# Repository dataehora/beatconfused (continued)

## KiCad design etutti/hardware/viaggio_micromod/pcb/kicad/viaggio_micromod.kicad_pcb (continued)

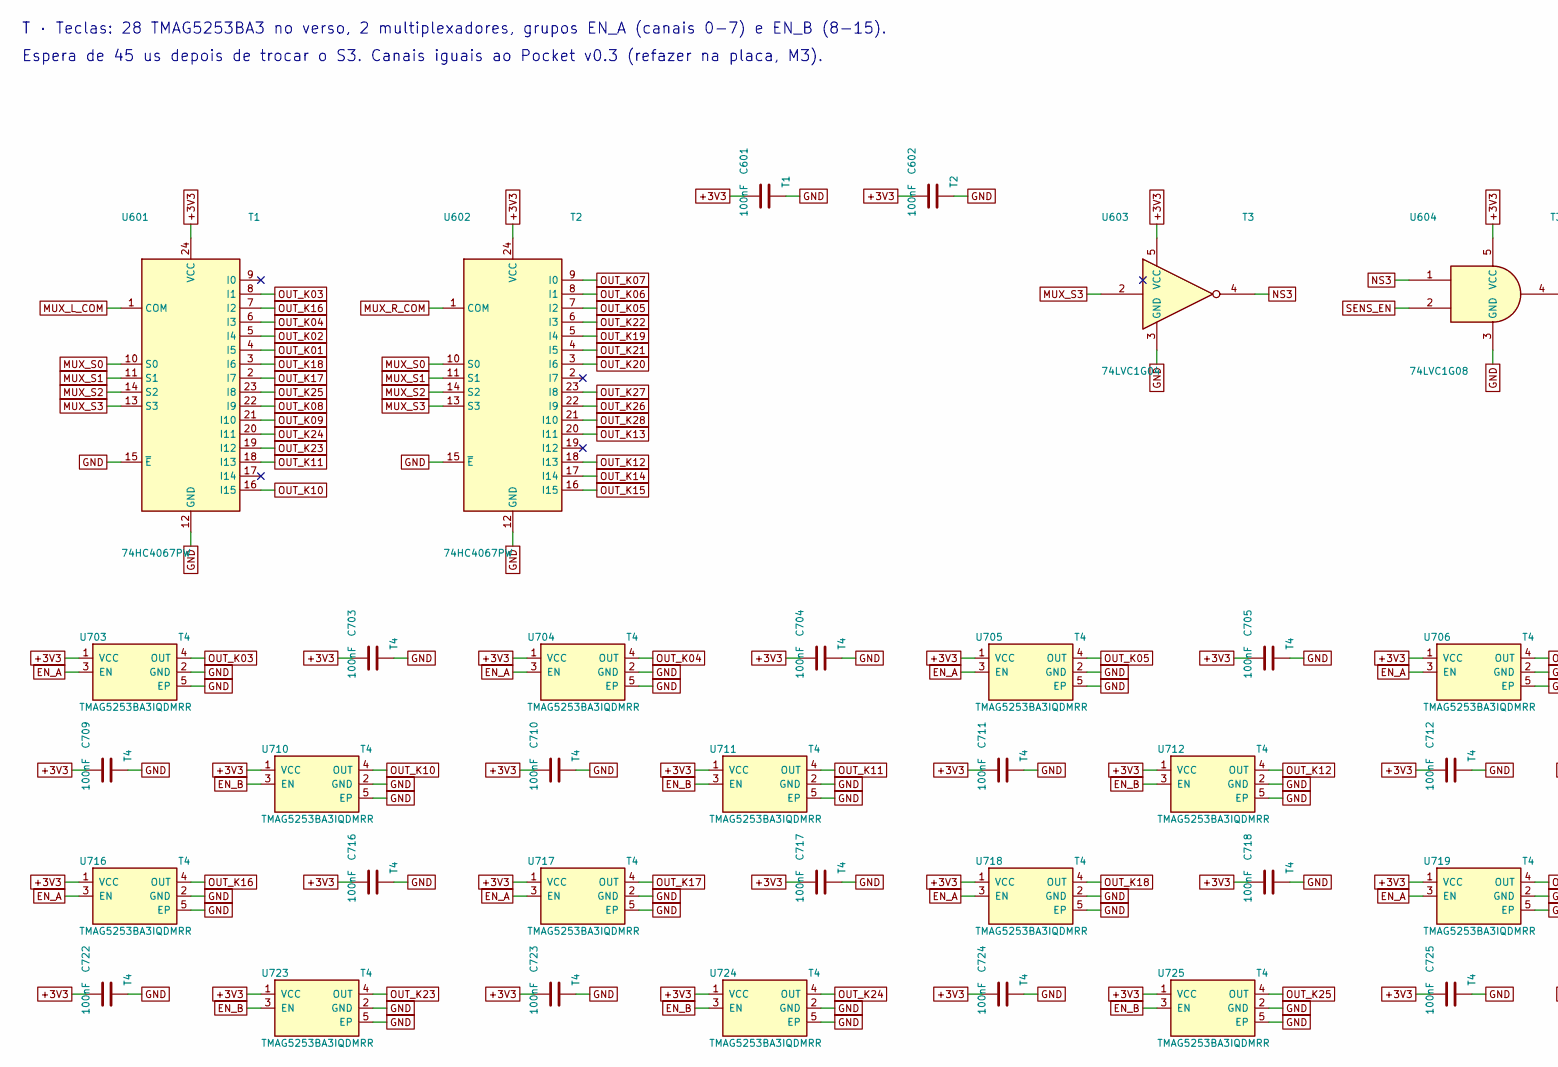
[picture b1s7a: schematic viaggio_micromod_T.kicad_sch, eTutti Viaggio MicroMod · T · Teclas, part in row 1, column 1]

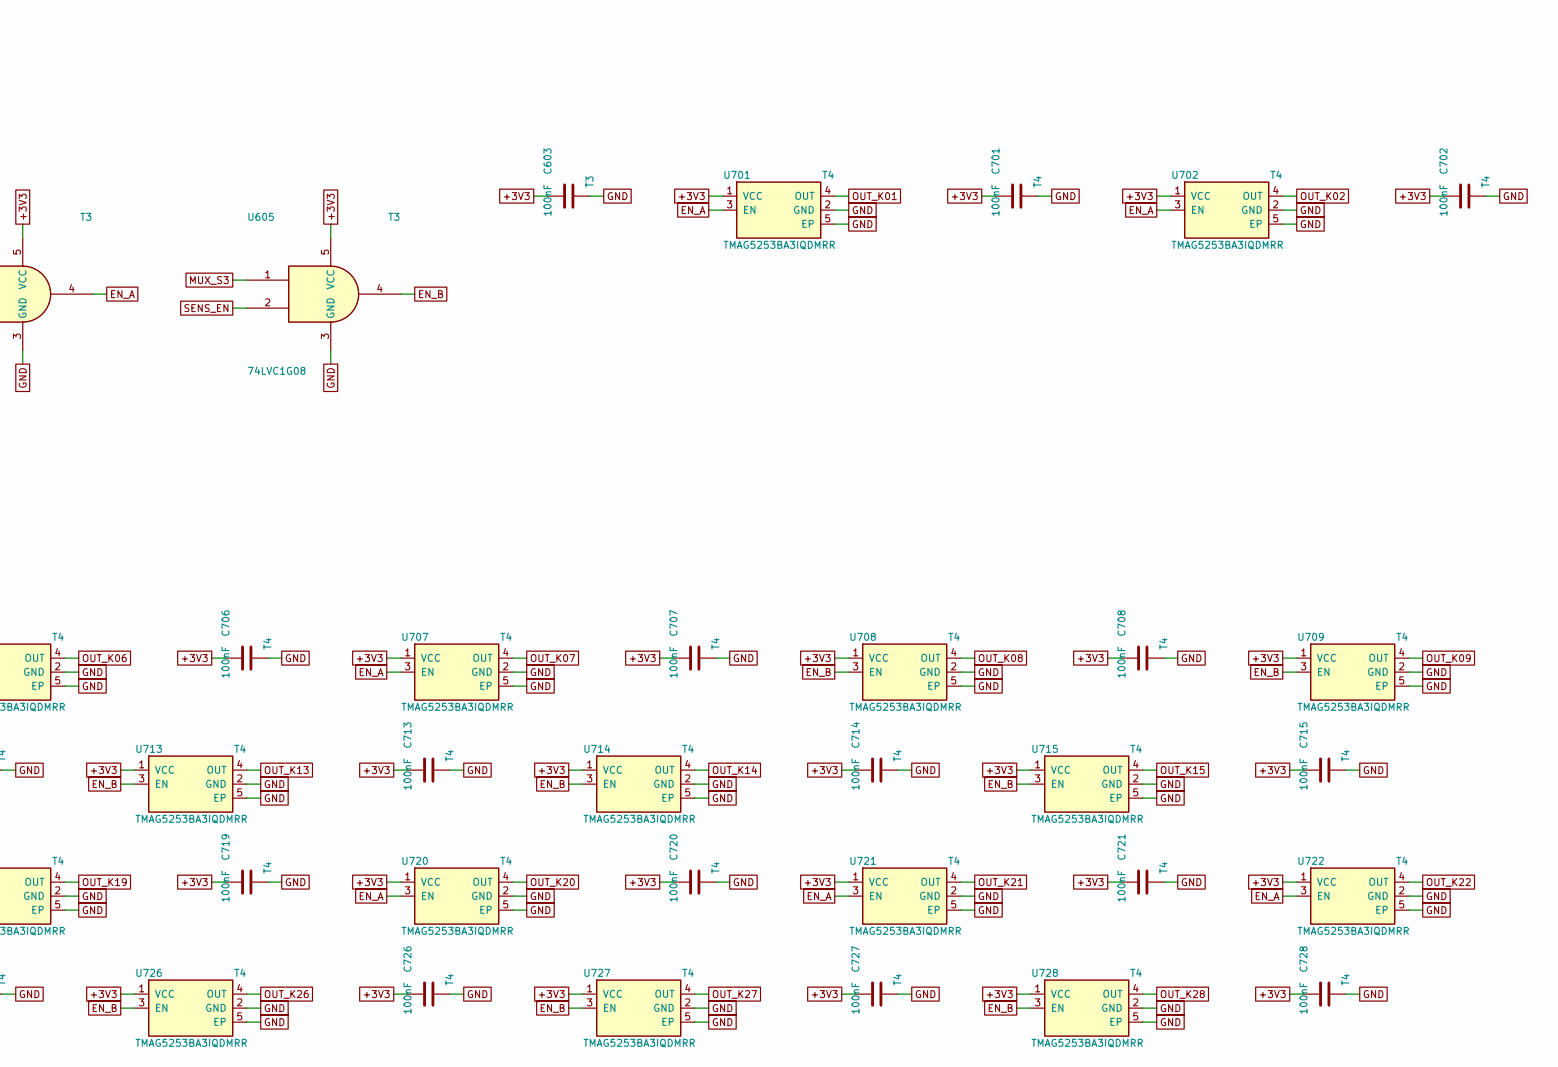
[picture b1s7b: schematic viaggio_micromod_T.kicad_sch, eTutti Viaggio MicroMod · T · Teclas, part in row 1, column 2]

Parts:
C601, C602, C603, C701, C702, C703, C704, C705, C706, C707, C708, C709, C710, C711, C712, C713, C714, C715, C716, C717, C718, C719, C720, C721, C722, C723, C724, C725, C726, C727, C728: 100nF; C_0402_1005Metric; LCSC C1525
U601, U602: 74HC4067PW; TSSOP-24_4.4x7.8mm_P0.65mm; LCSC C547038
U603: 74LVC1G04; SOT-23-5; LCSC C7827
U604, U605: 74LVC1G08; SOT-23-5; LCSC C7666
U701, U702, U703, U704, U705, U706, U707, U708, U709, U710, U711, U712, U713, U714, U715, U716, U717, U718, U719, U720, U721, U722, U723, U724, U725, U726, U727, U728: TMAG5253BA3IQDMRR; Texas_X2SON-4-1EP_1.1x1.4mm_P0.5mm_EP0.8x0.6mm

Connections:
+3V3: C601.1, C602.1, C603.1, C701.1, C702.1, C703.1, C704.1, C705.1, C706.1, C707.1, C708.1, C709.1, C710.1, C711.1, C712.1, C713.1, C714.1, C715.1, C716.1, C717.1, C718.1, C719.1, C720.1, C721.1, C722.1, C723.1, C724.1, C725.1, C726.1, C727.1, C728.1, U601.24 (VCC), U602.24 (VCC), U603.5 (VCC), U604.5 (VCC), U605.5 (VCC), U701.1 (VCC), U702.1 (VCC), U703.1 (VCC), U704.1 (VCC), U705.1 (VCC), U706.1 (VCC), U707.1 (VCC), U708.1 (VCC), U709.1 (VCC), U710.1 (VCC), U711.1 (VCC), U712.1 (VCC), U713.1 (VCC), U714.1 (VCC), U715.1 (VCC), U716.1 (VCC), U717.1 (VCC), U718.1 (VCC), U719.1 (VCC), U720.1 (VCC), U721.1 (VCC), U722.1 (VCC), U723.1 (VCC), U724.1 (VCC), U725.1 (VCC), U726.1 (VCC), U727.1 (VCC), U728.1 (VCC); also elsewhere on the board
EN_A: U604.4, U701.3 (EN), U702.3 (EN), U703.3 (EN), U704.3 (EN), U705.3 (EN), U706.3 (EN), U707.3 (EN), U716.3 (EN), U717.3 (EN), U718.3 (EN), U719.3 (EN), U720.3 (EN), U721.3 (EN), U722.3 (EN)
EN_B: U605.4, U708.3 (EN), U709.3 (EN), U710.3 (EN), U711.3 (EN), U712.3 (EN), U713.3 (EN), U714.3 (EN), U715.3 (EN), U723.3 (EN), U724.3 (EN), U725.3 (EN), U726.3 (EN), U727.3 (EN), U728.3 (EN)
GND: C601.2, C602.2, C603.2, C701.2, C702.2, C703.2, C704.2, C705.2, C706.2, C707.2, C708.2, C709.2, C710.2, C711.2, C712.2, C713.2, C714.2, C715.2, C716.2, C717.2, C718.2, C719.2, C720.2, C721.2, C722.2, C723.2, C724.2, C725.2, C726.2, C727.2, C728.2, U601.12 (GND), U601.15 (~E), U602.12 (GND), U602.15 (~E), U603.3 (GND), U604.3 (GND), U605.3 (GND), U701.2 (GND), U701.5 (EP), U702.2 (GND), U702.5 (EP), U703.2 (GND), U703.5 (EP), U704.2 (GND), U704.5 (EP), U705.2 (GND), U705.5 (EP), U706.2 (GND), U706.5 (EP), U707.2 (GND), U707.5 (EP), U708.2 (GND), U708.5 (EP), U709.2 (GND), U709.5 (EP), U710.2 (GND), U710.5 (EP), U711.2 (GND), U711.5 (EP), U712.2 (GND), U712.5 (EP), U713.2 (GND), U713.5 (EP), U714.2 (GND), U714.5 (EP), U715.2 (GND), U715.5 (EP), U716.2 (GND), U716.5 (EP), U717.2 (GND), U717.5 (EP), U718.2 (GND), U718.5 (EP), U719.2 (GND), U719.5 (EP), U720.2 (GND), U720.5 (EP), U721.2 (GND), U721.5 (EP), U722.2 (GND), U722.5 (EP), U723.2 (GND), U723.5 (EP), U724.2 (GND), U724.5 (EP), U725.2 (GND), U725.5 (EP), U726.2 (GND), U726.5 (EP), U727.2 (GND), U727.5 (EP), U728.2 (GND), U728.5 (EP); also elsewhere on the board
MUX_L_COM: U601.1 (COM); also elsewhere on the board
MUX_R_COM: U602.1 (COM); also elsewhere on the board
MUX_S0: U601.10 (S0), U602.10 (S0); also elsewhere on the board
MUX_S1: U601.11 (S1), U602.11 (S1); also elsewhere on the board
MUX_S2: U601.14 (S2), U602.14 (S2); also elsewhere on the board
MUX_S3: U601.13 (S3), U602.13 (S3), U603.2, U605.1; also elsewhere on the board
NS3: U603.4, U604.1
OUT_K01: U601.4 (I5), U701.4 (OUT)
OUT_K02: U601.5 (I4), U702.4 (OUT)
OUT_K03: U601.8 (I1), U703.4 (OUT)
OUT_K04: U601.6 (I3), U704.4 (OUT)
OUT_K05: U602.7 (I2), U705.4 (OUT)
OUT_K06: U602.8 (I1), U706.4 (OUT)
OUT_K07: U602.9 (I0), U707.4 (OUT)
OUT_K08: U601.22 (I9), U708.4 (OUT)
OUT_K09: U601.21 (I10), U709.4 (OUT)
OUT_K10: U601.16 (I15), U710.4 (OUT)
OUT_K11: U601.18 (I13), U711.4 (OUT)
OUT_K12: U602.18 (I13), U712.4 (OUT)
OUT_K13: U602.20 (I11), U713.4 (OUT)
OUT_K14: U602.17 (I14), U714.4 (OUT)
OUT_K15: U602.16 (I15), U715.4 (OUT)
OUT_K16: U601.7 (I2), U716.4 (OUT)
OUT_K17: U601.2 (I7), U717.4 (OUT)
OUT_K18: U601.3 (I6), U718.4 (OUT)
OUT_K19: U602.5 (I4), U719.4 (OUT)
OUT_K20: U602.3 (I6), U720.4 (OUT)
OUT_K21: U602.4 (I5), U721.4 (OUT)
OUT_K22: U602.6 (I3), U722.4 (OUT)
OUT_K23: U601.19 (I12), U723.4 (OUT)
OUT_K24: U601.20 (I11), U724.4 (OUT)
OUT_K25: U601.23 (I8), U725.4 (OUT)
OUT_K26: U602.22 (I9), U726.4 (OUT)
OUT_K27: U602.23 (I8), U727.4 (OUT)
OUT_K28: U602.21 (I10), U728.4 (OUT)
SENS_EN: U604.2, U605.2; also elsewhere on the board

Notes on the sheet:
T · Teclas: 28 TMAG5253BA3 no verso, 2 multiplexadores, grupos EN_A (canais 0-7) e EN_B (8-15).
Espera de 45 us depois de trocar o S3. Canais iguais ao Pocket v0.3 (refazer na placa, M3).

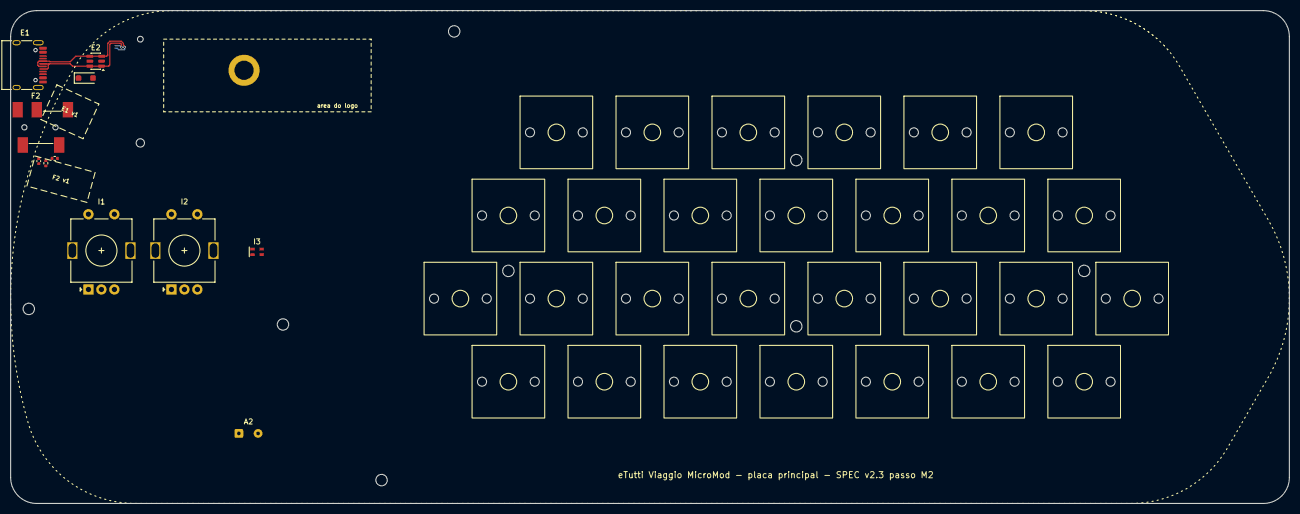
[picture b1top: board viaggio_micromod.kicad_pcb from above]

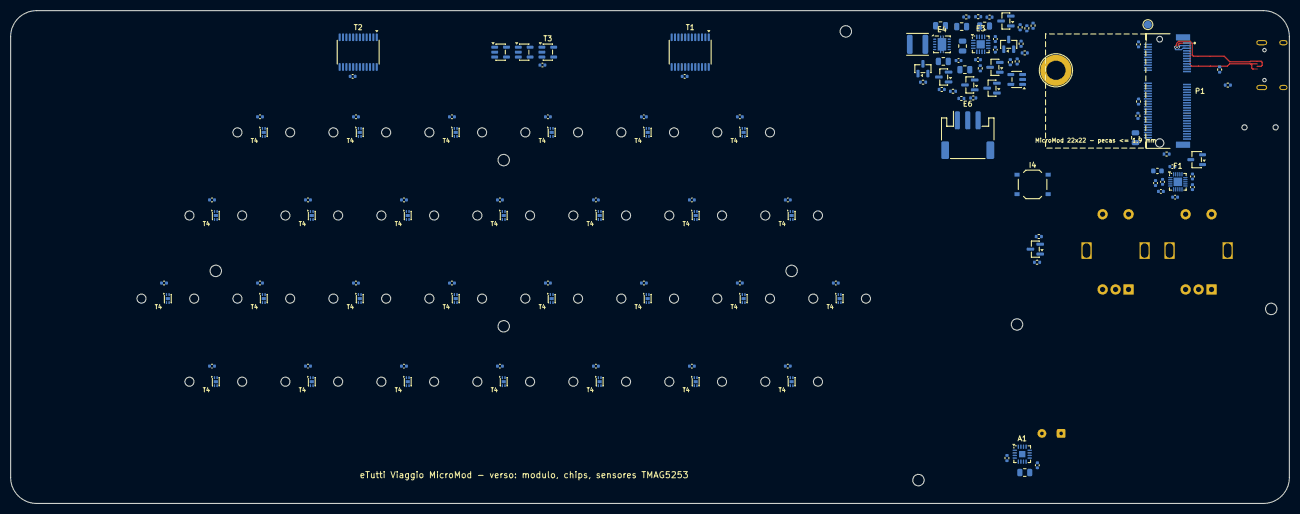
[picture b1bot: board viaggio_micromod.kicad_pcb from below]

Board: 4 copper layers, 246.5 x 95.0 mm, 177 parts (130 on the bottom side), 99 nets.

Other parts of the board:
H1, H2, H3, H4, H5, H6, H7, H8: MountingHole_2.2mm_M2
SW1, SW2, SW3, SW4, SW5, SW6, SW7, SW8, SW9, SW10, SW11, SW12, SW13, SW14, SW15, SW16, SW17, SW18, SW19, SW20, SW21, SW22, SW23, SW24, SW25, SW26, SW27, SW28: Gateron_Magnetic_MX_1u

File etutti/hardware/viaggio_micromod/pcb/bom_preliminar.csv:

codigo,referencias,qtd,valor_peca,encapsulamento,lcsc,classe_jlc,preco_unit_usd_est,montagem,status,nota
P1,MOD1,1,SparkFun MicroMod Teensy Processor (DEV-16402),M.2 2222 Key E,-,-,24.950,"em casa (encaixar no J101, apertar o parafuso)",final,"i.MX RT1062 600 MHz, 16 MB flash, 1 MB RAM, bootloader MKL02; fqbn teensy:avr:teensyMM"
P1,SCR1,1,"parafuso M2.5 x 3, cabeca chata (Phillips)",-,-,-,0.050,em casa,conferir,prende o modulo no espacador H101 (vem no KIT-16549 da SparkFun)
P1,R105,1,100,R_0402_1005Metric,C25076,basica,0.001,JLC,final,"MCLK 11,3 MHz: em serie, junto do J101 (SPEC 4, 5o)"
P1,C102,1,100nF,C_0402_1005Metric,C1525,basica,0.001,JLC,final,
P1,C101,1,10uF,C_0805_2012Metric,C15850,basica,0.008,JLC,final,"3,3 V junto dos pads 2/74 do J101"
P1,J101,1,91302-42-067RCE,M.2_E_H4.2_UMAX_91302-42-067,C48985906,estendida,1.260,JLC,conferir,"UMAX M.2 Key E 67 pinos, 0,5 mm, 4,2 mm (estoque LCSC 622 em 25 out 2026; o LOTES C841659 estava com 0); footprint pelo desenho UMAX C-91302-42 rev C; no verso; modulo SparkFun MicroMod Teensy DEV-16402 encaixado em casa"
P1,H101,1,9774025151R,Standoff_SMD_M2.5_H2.5,-,-,0.600,JLC (Global Sourcing),conferir,"espacador SMD M2.5 x 2,5 mm (Wurth WA-SMSI, o da SparkFun; SPEC v2.3); a (+4,0; -20,0) do J101 nas coordenadas do footprint; sem equivalente LCSC de 2,5 mm com estoque em 25 out 2026 (YIYUAN SMTSOM2.520BTR C5301776: 2,0 mm, estoque 0); parafuso M2.5 x 3 cabeca chata em casa"
P1,TP101,1,RESET#/ONOFF,TestPoint_Pad_D1.5mm,-,-,0.000,sem peca (pad),final,pad 6 do MicroMod = ONOFF do RT1062 no modulo Teensy (nao e o POR_B); ver ELETRONICA.md
E1,R201 R202,2,5.1k,R_0402_1005Metric,C25905,basica,0.001,JLC,final,
E1,J201,1,TYPE-C-31-M-12,USB_C_Receptacle_HRO_TYPE-C-31-M-12,C165948,estendida,0.150,JLC,final,"lado de cima, borda esquerda, boca para fora"
E2,D201,1,SMF5.0A,D_SOD-123F,C151296,estendida,0.050,JLC,final,"TVS do VBUS (Pocket D60); lado de cima, junto do USB-C (SPEC v2.3)"
E2,U201,1,USBLC6-2SC6,SOT-23-6,C7519,basica,0.050,JLC,conferir,"lado de cima, junto do USB-C (SPEC v2.3)"
E3,R204,1,1.5k,R_0402_1005Metric,C25867,basica,0.001,JLC,conferir,"so vale com EN2=1 (1,07 A); obrigatorio"
E3,R203,1,1.8k,R_0402_1005Metric,C25811,basica,0.001,JLC,conferir,"ICHG = 890/1800 = 0,49 A"
E3,R206 R210 R211 R213 R215 R218,6,100k,R_0402_1005Metric,C25741,basica,0.001,JLC,final,
E3,C204 C205,2,100nF,C_0402_1005Metric,C1525,basica,0.001,JLC,final,
E3,R205 R214,2,10k,R_0402_1005Metric,C25744,basica,0.001,JLC,final,
E3,C201 C202 C203,3,10uF,C_0805_2012Metric,C15850,basica,0.008,JLC,final,
E3,R208 R209 R212,3,1M,R_0402_1005Metric,C26083,basica,0.001,JLC,final,medida da bateria: V(pino 16) = VBAT/2
E3,R207 R217,2,1k,R_0402_1005Metric,C11702,basica,0.001,JLC,final,
E3,C213,1,1uF,C_0402_1005Metric,C52923,basica,0.002,JLC,final,"100 ms: depois do desligamento o PWR_EN_S nao sobe antes de o 3,3 V cair (sem religar)"
E3,U203,1,74LVC1G08,SOT-23-5,C7666,estendida,0.030,JLC,final,USB_HOLD = USB presente E PWR_EN alto (alimentada pelo 3V3)
E3,Q202,1,AO3400A,SOT-23,C20917,basica,0.010,JLC,final,"ligado, a luz de carga apaga (Pocket Q31)"
E3,Q201 Q203,2,AO3401A,SOT-23,C15127,basica,0.010,JLC,final,luz de carga (Pocket Q30)
E3,D202 D203 D204 D205,4,BAT54C,SOT-23,C134405,estendida,0.020,JLC,final,leitura do ~CHG pelo pino 26 (so com USB)
E3,U202,1,BQ24074RGTR,VQFN-16-1EP_3x3mm_P0.5mm_EP1.6x1.6mm,C54313,estendida,1.100,JLC,final,"USB500 (EN2=0, EN1=1), 500 mA, NTC no TS; TMR e ITERM abertos = padrao; OUT 4,4 V com USB"
E4,R216,1,100,R_0402_1005Metric,C25076,basica,0.001,JLC,final,
E4,C209,1,100nF,C_0402_1005Metric,C1525,basica,0.001,JLC,final,
E4,C206 C207 C208,3,10uF,C_0805_2012Metric,C15850,basica,0.008,JLC,final,
E4,L201,1,2.2uH,L_Changjiang_FNR4020S,C167825,estendida,0.080,JLC,final,FNR4020S2R2MT (Pocket L10)
E4,U204,1,TPS63001DRCR,Texas_DRC0010J,C28060,estendida,1.400,JLC,final,"3,3 V fixo; PS/SYNC baixo = economia; EN = EN_REQ (sem a porta U206 da v2.1)"
E6,J202,1,S3B-PH-SM4-TB,JST_PH_S3B-PH-SM4-TB_1x03-1MP_P2.00mm_Horizontal,C265101,estendida,0.300,JLC,final,"bateria 1 = +, 2 = NTC, 3 = - (ordem do Pocket; conferir o cabo)"
F1,C302 C304 C305,3,100nF,C_0402_1005Metric,C1525,basica,0.001,JLC,final,
F1,C307,1,150nF,C_0402_1005Metric,-,estendida,0.003,JLC,conferir,"Audio Board: 0,15 uF"
F1,R301 R302,2,2.2k,R_0402_1005Metric,C25879,basica,0.001,JLC,conferir,
F1,C301 C303 C306,3,2.2uF,C_0402_1005Metric,C12530,basica,0.003,JLC,conferir,
F1,FB301,1,600R@100MHz,L_0603_1608Metric,-,basica,0.005,JLC,conferir,Audio Board: Ferrite 600 no VDDA
F1,U301,1,SGTL5000XNLA3,QFN-20-1EP_3x3mm_P0.4mm_EP1.65x1.65mm,C511764,estendida,1.800,JLC,conferir,como a Audio Board Rev D2 (endereco I2C fixo 0x0A); sem entrada de linha/microfone
F1,U302,1,XC6206P182MR,SOT-23-3,C347373,estendida,0.030,JLC,conferir,"1,8 V do VDDD (a Audio Board usa AP7313)"
F2,R303,1,100k,R_0402_1005Metric,C25741,basica,0.001,JLC,final,
F2,C308,1,100nF,C_0402_1005Metric,C1525,basica,0.001,JLC,final,
F2,R304,1,1M,R_0402_1005Metric,C26083,basica,0.001,JLC,final,
F2,J301,1,PJ-327A 5JJ,Jack_3.5mm_PJ-327A_SMD,C668605,estendida,0.100,JLC,conferir,"SMD, angulo reto, SHOU HAN; 1/2 manga (HP_VGND, nunca no GND), 3 anel, 4 ponta, 5 contato da ponta (fechado sem plugue)"
I1,SW401,1,EC11E18244A5,RotaryEncoder_Alps_EC11E-Switch_Vertical_H20mm,C255515,estendida,1.200,JLC,final,volume; clique de 2 s liga/desliga; 18 pulsos / 36 detentes (o 15/15 nao tem estoque): ENC_STEPS_PER_DETENT = 2
I2,SW402,1,EC11E18244A5,RotaryEncoder_Alps_EC11E-Switch_Vertical_H20mm,C255515,estendida,1.200,JLC,final,seletor; clique = funcoes de som; 18 pulsos / 36 detentes (o 15/15 nao tem estoque): ENC_STEPS_PER_DETENT = 2
I3,R401,1,270,R_0402_1005Metric,C25190,basica,0.001,JLC,conferir,
I3,R402,1,330,R_0402_1005Metric,C25104,basica,0.001,JLC,conferir,
I3,D402,1,BAT54C,SOT-23,C134405,estendida,0.020,JLC,final,OU do vermelho: luz de carga e firmware (Pocket D30)
I3,D401,1,TJ-S1615SW6TGLCRG-A5,LED_1615_RG_4pad,C273605,estendida,0.020,JLC,final,"1615 vermelho/verde; pads do datasheet: 1 = anodo vermelho, 2 = catodo vermelho, 3 = anodo verde, 4 = catodo verde"
I4,SW403,1,Program,SW_Push_1P1T_XKB_TS-1187A,C318884,basica,0.020,JLC,conferir,"no verso, por um furo no fundo; 5,1 x 5,1 (a SPEC pedia 4 x 4)"
A1,C502,1,100nF,C_0402_1005Metric,C1525,basica,0.001,JLC,final,
A1,C501,1,10uF,C_0805_2012Metric,C15850,basica,0.008,JLC,final,
A1,R501,1,680k,R_0402_1005Metric,-,estendida,0.002,JLC,conferir,"com os 100k internos: 0,42 V no SD_MODE = (L+R)/2; pino baixo = desligado"
A1,U501,1,MAX98357AETE+T,TQFN-16-1EP_3x3mm_P0.5mm_EP1.23x1.23mm,C910544,estendida,1.400,JLC,final,GAIN_SLOT aberto = 9 dB; mono (L+R)/2 pelo divisor do SD_MODE
A2,J501,1,alto-falante (fios),SolderWire-0.127sqmm_1x02_P3.7mm_D0.48mm_OD1mm,-,-,0.000,sem peca (pads; fios do A2 soldados em casa),conferir,
T1,C601,1,100nF,C_0402_1005Metric,C1525,basica,0.001,JLC,final,
T1,U601,1,74HC4067PW,TSSOP-24_4.4x7.8mm_P0.65mm,C547038,estendida,0.250,JLC,final,"esquerdo (metade baixa do teclado), COM no pino 15; canais = Pocket v0.3"
T2,C602,1,100nF,C_0402_1005Metric,C1525,basica,0.001,JLC,final,
T2,U602,1,74HC4067PW,TSSOP-24_4.4x7.8mm_P0.65mm,C547038,estendida,0.250,JLC,final,"direito (metade alta), COM no pino 14; canais = Pocket v0.3"
T3,C603,1,100nF,C_0402_1005Metric,C1525,basica,0.001,JLC,final,
T3,U603,1,74LVC1G04,SOT-23-5,C7827,estendida,0.030,JLC,final,
T3,U604 U605,2,74LVC1G08,SOT-23-5,C7666,estendida,0.030,JLC,final,EN_A = SENS_EN e S3 baixo (canais 0-7)
T4,C701 C702 C703 C704 C705 C706 C707 C708 C709 C710 C711 C712 C713 C714 C715 C716 C717 C718 C719 C720 C721 C722 C723 C724 C725 C726 C727 C728,28,100nF,C_0402_1005Metric,C1525,basica,0.001,JLC,final,
T4,U701 U702 U703 U704 U705 U706 U707 U708 U709 U710 U711 U712 U713 U714 U715 U716 U717 U718 U719 U720 U721 U722 U723 U724 U725 U726 U727 U728,28,TMAG5253BA3IQDMRR,Texas_X2SON-4-1EP_1.1x1.4mm_P0.5mm_EP0.8x0.6mm,-,-,0.450,Global Sourcing (JLCPCB),conferir,"tecla SW1 (fileira 1, A3); verso, mesma orientacao do Pocket"

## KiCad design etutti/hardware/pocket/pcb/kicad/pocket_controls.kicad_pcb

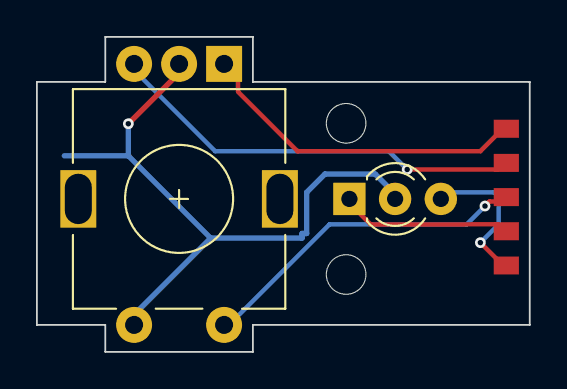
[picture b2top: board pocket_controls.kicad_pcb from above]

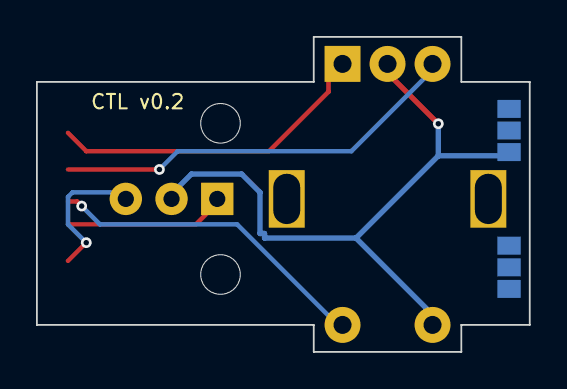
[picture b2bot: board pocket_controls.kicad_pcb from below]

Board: 2 copper layers, 27.4 x 17.5 mm, 15 parts (6 on the bottom side), 6 nets.

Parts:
D1: LED 3mm R/G CC; LED_D3.0mm-3
H1, H2: MountingHole_2.2mm_M2
JP2, JP3, JP4, JP5, JP6, JP7: (no value)
JW6, JW7, JW8, JW9, JW10: (no value)
SW1: EC11E 15/15; RotaryEncoder_Alps_EC11E-Switch_Vertical_H20mm

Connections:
ENC_A: JW6.1, SW1.A
ENC_B: JW7.1, SW1.B
ENC_SW: JW8.1, SW1.S2
GND: D1.2, JP4.1, SW1.C, SW1.S1
LED_G: D1.3, JW10.1
LED_R: D1.1, JW9.1

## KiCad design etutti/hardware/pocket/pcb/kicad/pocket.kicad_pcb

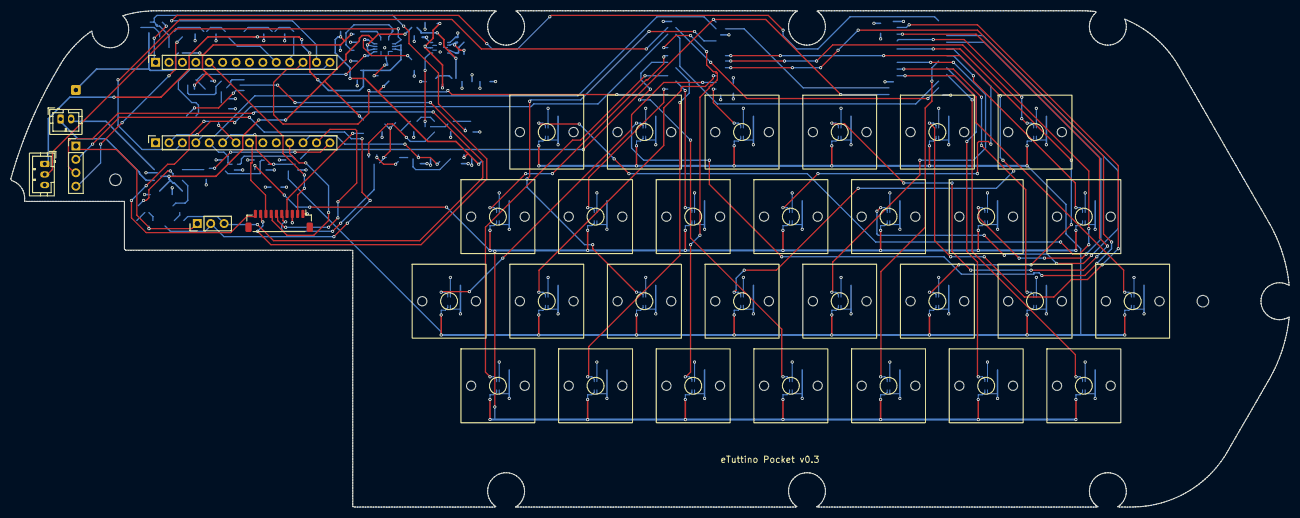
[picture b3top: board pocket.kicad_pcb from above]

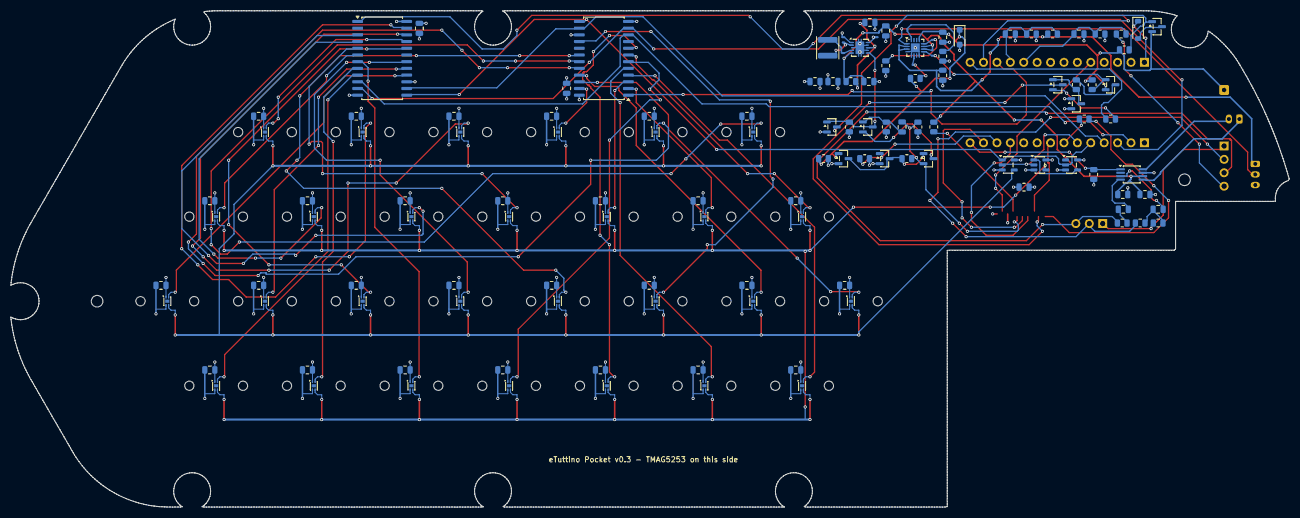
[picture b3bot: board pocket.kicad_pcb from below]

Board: 4 copper layers, 242.2 x 94.0 mm, 155 parts (117 on the bottom side), 85 nets.

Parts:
C1, C2, C3, C4, C5, C6, C7, C8, C9, C10, C11, C12, C13, C14, C15, C16, C17, C18, C19, C20, C21, C22, C23, C24, C25, C26, C27, C28, C40, C41, C42, C43, C55, C66, C71, C72: 100nF; C_0805_2012Metric
C60, C61, C62, C63, C64, C65, C67: 10uF; C_0805_2012Metric
C68, C81: 1uF; C_0805_2012Metric
D20, D30: BAT54C; SOT-23
D60: SMF5.0A; D_SOD-123F
D61: B5819W; D_SOD-123
H1, H2: MountingHole_2.2mm_M2
J1, J2: PinSocket_1x14_P2.54mm_Vertical
J_BAT: battery 3-wire (+, NTC, -); JST_PH_B3B-PH-K_1x03_P2.00mm_Vertical
J_CTL: controls board; JST_SH_BM10B-SRSS-TB_1x10-1MP_P1.00mm_Vertical
J_HP: wires from the Audio Board's jack; PinHeader_1x03_P2.54mm_Vertical
J_JACK: wires from the panel jack (T, R, S, tip switch); PinHeader_1x04_P2.54mm_Vertical
J_SPK: speaker; JST_PH_B2B-PH-K_1x02_P2.00mm_Vertical
J_VBUS: VBUS wire from the Teensy's VUSB pad; SolderWire-0.25sqmm_1x01_D0.65mm_OD1.7mm
L10: 2.2uH 4x4; L_Changjiang_FNR4020S
Q20, Q23, Q30: AO3401A; SOT-23
Q21, Q22, Q24, Q31: AO3400A; SOT-23
R10: 1.8k; R_0805_2012Metric
R11: 1.5k; R_0805_2012Metric
R12: 10k; R_0805_2012Metric
R13, R20: 100; R_0805_2012Metric
R21, R22, R23, R40, R41, R43: 1M; R_0805_2012Metric
R24, R25, R26, R27, R30, R42, R44: 100k; R_0805_2012Metric
R31: 1k; R_0805_2012Metric
R32: 270; R_0805_2012Metric
R33: 330; R_0805_2012Metric
R45, R46: 68k; R_0805_2012Metric
R47: 33k; R_0805_2012Metric
SW1, SW2, SW3, SW4, SW5, SW6, SW7, SW8, SW9, SW10, SW11, SW12, SW13, SW14, SW15, SW16, SW17, SW18, SW19, SW20, SW21, SW22, SW23, SW24, SW25, SW26, SW27, SW28: Gateron_Magnetic_MX_1u
U1, U2, U3, U4, U5, U6, U7, U8, U9, U10, U11, U12, U13, U14, U15, U16, U17, U18, U19, U20, U21, U22, U23, U24, U25, U26, U27, U28: TMAG5253BA3IQDMRR; Texas_X2SON-4-1EP_1.1x1.4mm_P0.5mm_EP0.8x0.6mm
U51, U52: CD74HC4067M96; SOIC-24W_7.5x15.4mm_P1.27mm
U53: 74LVC1G04; SOT-23-5
U54, U55: 74LVC1G08; SOT-23-5
U60: BQ24074RGTR; QFN-16-1EP_3x3mm_P0.5mm_EP1.7x1.7mm
U61: TPS63001DRCR; Texas_DRC0010J
U62: PAM8302AASCR; MSOP-8_3x3mm_P0.65mm

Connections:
AMP_N: C43.1, R47.2
AMP_P: C42.1, R45.2, R46.2
AMP_SD: J1.14, R44.1, U62.1
BAT: C62.1, J_BAT.1, R40.1, U60.2, U60.3
CHG: Q30.1, R30.2, U60.9
CHGA: D30.1, Q31.3, R31.2
CHGLED: Q30.3, R31.1
COM0: J2.13, U51.1
COM1: J2.12, U52.1
EN1: R12.2, U60.6
ENC_A: J1.13, J_CTL.6
ENC_B: J1.11, J_CTL.7
ENC_SW: J1.8, J_CTL.8
EN_A: U1.3, U2.3, U3.3, U4.3, U5.3, U6.3, U7.3, U16.3, U17.3, U18.3, U19.3, U20.3, U21.3, U22.3, U54.4
EN_B: U8.3, U9.3, U10.3, U11.3, U12.3, U13.3, U14.3, U15.3, U23.3, U24.3, U25.3, U26.3, U27.3, U28.3, U55.4
EN_BB: D20.3, Q24.1, R23.1, U61.6
GND: C1.1, C2.1, C3.1, C4.1, C5.1, C6.1, C7.1, C8.1, C9.1, C10.1, C11.1, C12.1, C13.1, C14.1, C15.1, C16.1, C17.1, C18.1, C19.1, C20.1, C21.1, C22.1, C23.1, C24.1, C25.1, C26.1, C27.1, C28.1, C40.2, C41.2, C55.2, C60.2, C61.2, C62.2, C63.2, C64.2, C65.2, C66.2, C67.2, C68.2, C71.2, C72.1, D60.2, J1.1, J2.2, J_BAT.3, J_CTL.3, Q21.2, Q22.2, Q24.2, Q31.2, R10.2, R11.2, R21.2, R22.2, R23.2, R25.2, R26.2, R41.2, R43.2, R44.2, U1.2, U2.2, U3.2, U4.2, U5.2, U6.2, U7.2, U8.2, U9.2, U10.2, U11.2, U12.2, U13.2, U14.2, U15.2, U16.2, U17.2, U18.2, U19.2, U20.2, U21.2, U22.2, U23.2, U24.2, U25.2, U26.2, U27.2, U28.2, U51.12, U51.15, U52.12, U52.15, U53.3, U54.3, U55.3, U60.4, U60.5, U60.8, U60.17, U61.3, U61.7, U61.9, U61.11, U62.7
HOLD: D20.2, Q20.3
HP_DET: C41.1, J2.10, R42.2, R43.1
HP_L: J_HP.1, J_JACK.1, R45.1
HP_R: J_HP.2, J_JACK.2, R46.1
HP_TIPSW: J_JACK.4, R42.1
HP_VGND: J_HP.3, J_JACK.3, R47.1
ILIM: R11.1, U60.12
INN: C43.2, U62.4
INP: C42.2, U62.3
ISET: R10.1, U60.16
KEEP: J1.12, Q21.1, R25.1
L1: L10.1, U61.4
L2: L10.2, U61.2
LEDR_A: D30.2, R32.2
LED_G: J_CTL.10, R33.2
LED_G_DRV: J1.7, R33.1
LED_R: D30.3, J_CTL.9
LED_R_DRV: J2.14, R32.1
NS3: U53.4, U54.1
OUT_U1: U1.4, U52.4
OUT_U2: U2.4, U52.5
OUT_U3: U3.4, U52.8
OUT_U4: U4.4, U52.6
OUT_U5: U5.4, U51.7
OUT_U6: U6.4, U51.8
OUT_U7: U7.4, U51.9
OUT_U8: U8.4, U52.22
OUT_U9: U9.4, U52.21
OUT_U10: U10.4, U52.16
OUT_U11: U11.4, U52.18
OUT_U12: U12.4, U51.18
OUT_U13: U13.4, U51.20
OUT_U14: U14.4, U51.17
OUT_U15: U15.4, U51.16
OUT_U16: U16.4, U52.7
OUT_U17: U17.4, U52.2
OUT_U18: U18.4, U52.3
OUT_U19: U19.4, U51.5
OUT_U20: U20.4, U51.3
OUT_U21: U21.4, U51.4
OUT_U22: U22.4, U51.6
OUT_U23: U23.4, U52.19
OUT_U24: U24.4, U52.20
OUT_U25: U25.4, U52.23
OUT_U26: U26.4, U51.22
OUT_U27: U27.4, U51.23
OUT_U28: U28.4, U51.21
POT: J2.5, J_CTL.2
PULSE: C81.2, D20.1, R22.1
PWR_A: J_CTL.4, R20.2
PWR_B: C81.1, J_CTL.5, Q20.2, R21.1, R24.2
QSG: Q20.1, Q21.3, Q22.3, R24.1
QVG: Q23.1, Q24.3, R27.2
SEL0: J1.2, U51.10, U52.10
SEL1: J1.3, U51.11, U52.11
SEL2: J1.4, U51.14, U52.14
SEL3: J1.5, U51.13, U52.13, U53.2, U55.1
SENS_EN: J1.6, U54.2, U55.2
SPK_N: J_SPK.2, U62.8
SPK_P: J_SPK.1, U62.5
TS: J_BAT.2, U60.1
VBAT_S: C40.1, J2.11, R40.2, R41.1
VBUS: C60.1, D60.1, J_VBUS.1, Q22.1, Q23.2, Q30.2, R12.1, R26.1, R27.1, R30.1, U60.13
VCC: C1.2, C2.2, C3.2, C4.2, C5.2, C6.2, C7.2, C8.2, C9.2, C10.2, C11.2, C12.2, C13.2, C14.2, C15.2, C16.2, C17.2, C18.2, C19.2, C20.2, C21.2, C22.2, C23.2, C24.2, C25.2, C26.2, C27.2, C28.2, C55.1, C64.1, C65.1, C71.1, C72.2, J2.3, J_CTL.1, Q31.1, U1.1, U2.1, U3.1, U4.1, U5.1, U6.1, U7.1, U8.1, U9.1, U10.1, U11.1, U12.1, U13.1, U14.1, U15.1, U16.1, U17.1, U18.1, U19.1, U20.1, U21.1, U22.1, U23.1, U24.1, U25.1, U26.1, U27.1, U28.1, U51.24, U52.24, U53.5, U54.5, U55.5, U61.1, U61.10
VINA: C66.1, R13.2, U61.8
VIN_D: D61.2, Q23.3
VIN_T: D61.1, J2.1
VSYS: C61.1, C63.1, C67.1, C68.1, R13.1, R20.1, U60.10, U60.11, U61.5, U62.6

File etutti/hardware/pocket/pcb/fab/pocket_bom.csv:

Comment,Designator,Footprint,LCSC Part #
"TMAG5253BA3IQDMRR (CONSIGNED / global sourcing: not stocked at LCSC)","U1,U2,U3,U4,U5,U6,U7,U8,U9,U10,U11,U12,U13,U14,U15,U16,U17,U18,U19,U20,U21,U22,U23,U24,U25,U26,U27,U28","X2SON-4 1.1x1.4",""
"100nF 0805 X7R","C1,C2,C3,C4,C5,C6,C7,C8,C9,C10,C11,C12,C13,C14,C15,C16,C17,C18,C19,C20,C21,C22,C23,C24,C25,C26,C27,C28,C71,C72","C_0805","C49678"
"CD74HC4067M96","U51,U52","SOIC-24W","C98457"
"BQ24074RGTR","U60","QFN-16-1EP_3x3mm_P0.5mm_EP1.7x1.7mm","C54313"
"10uF","C60,C61,C62,C63,C64,C65,C67","C_0805_2012Metric","C15850"
"SMF5.0A","D60","D_SOD-123F","C151296"
"1.8k","R10","R_0805_2012Metric","C1358"
"1.5k","R11","R_0805_2012Metric","C4310"
"10k","R12","R_0805_2012Metric","C17414"
"TPS63001DRCR","U61","Texas_DRC0010J","C28060"
"2.2uH 4x4","L10","L_Changjiang_FNR4020S","C167825"
"100","R13,R20","R_0805_2012Metric","C17408"
"100nF","C66,C40,C41,C42,C43,C55","C_0805_2012Metric","C49678"
"1M","R21,R22,R23,R40,R41,R43","R_0805_2012Metric","C17514"
"1uF","C81,C68","C_0805_2012Metric","C28323"
"BAT54C","D20,D30","SOT-23","C134405"
"AO3401A","Q20,Q23,Q30","SOT-23","C15127"
"100k","R24,R25,R26,R27,R30,R42,R44","R_0805_2012Metric","C17407"
"AO3400A","Q21,Q22,Q24,Q31","SOT-23","C20917"
"B5819W","D61","D_SOD-123","C8598"
"1k","R31","R_0805_2012Metric","C17513"
"270","R32","R_0805_2012Metric","C17590"
"330","R33","R_0805_2012Metric","C17630"
"PAM8302AASCR","U62","MSOP-8_3x3mm_P0.65mm","C113367"
"68k","R45,R46","R_0805_2012Metric","C17801"
"33k","R47","R_0805_2012Metric",""
"74LVC1G04","U53","SOT-23-5","C7827"
"74LVC1G08","U54,U55","SOT-23-5","C7666"
"battery 3-wire (+, NTC, -)","J_BAT","JST_PH_B3B-PH-K_1x03_P2.00mm_Vertical","C131339"
"speaker","J_SPK","JST_PH_B2B-PH-K_1x02_P2.00mm_Vertical","C131337"
"controls board","J_CTL","JST_SH_BM10B-SRSS-TB_1x10-1MP_P1.00mm_Vertical","C160396"

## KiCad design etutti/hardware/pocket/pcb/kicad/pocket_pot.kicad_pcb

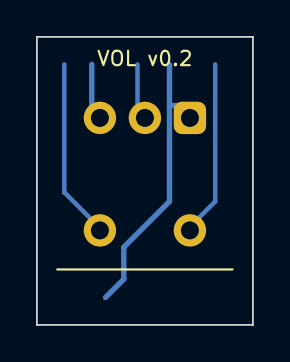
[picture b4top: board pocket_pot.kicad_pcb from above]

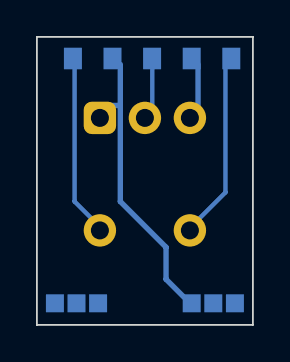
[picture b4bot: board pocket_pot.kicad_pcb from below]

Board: 2 copper layers, 12.0 x 16.0 mm, 12 parts (11 on the bottom side), 5 nets.

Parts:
JP1, JP2, JP3, JP4, JP5, JP6: (no value)
JW1, JW2, JW3, JW4, JW5: (no value)
RV1: RK097 A10k + SPST; Potentiometer_Alps_RK097_Single_Horizontal_Switch

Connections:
GND: JP3.1, JW3.1, RV1.1
POT: JW2.1, RV1.2
PWR_A: JW4.1, RV1.4
PWR_B: JW5.1, RV1.5
VCC: JW1.1, RV1.3

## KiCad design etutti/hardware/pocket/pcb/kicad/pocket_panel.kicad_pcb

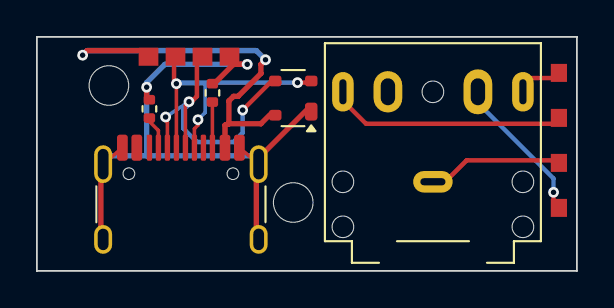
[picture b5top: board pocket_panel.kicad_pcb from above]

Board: 2 copper layers, 30.0 x 13.0 mm, 15 parts (0 on the bottom side), 11 nets.

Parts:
H1, H2: MountingHole_2.2mm_M2
J1: TYPE-C-31-M-12; USB_C_Receptacle_HRO_TYPE-C-31-M-12
J2: SJ1-3525N; Jack_3.5mm_CUI_SJ1-3525N_Horizontal
R1, R2: 5.1k; R_0402_1005Metric
TP1, TP2, TP3, TP4, TP5, TP6, TP7, TP8: (no value)
U1: PRTR5V0U2X; SOT-143

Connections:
CC1: J1.A5, R1.1
CC2: J1.B5, R2.1
DM: J1.A7, J1.B7, TP3.1, U1.3
DP: J1.A6, J1.B6, TP2.1, U1.2
GND: J1.A1, J1.A12, J1.B1, J1.B12, J1.SH, R1.2, R2.2, TP4.1, U1.1
HP_L: J2.T, TP5.1
HP_R: J2.R, TP6.1
HP_TIPSW: J2.TN, TP8.1
HP_VGND: J2.S, TP7.1
VBUS: J1.A9, J1.B4, TP1.1, U1.4
VBUS_L: J1.A4, J1.B9

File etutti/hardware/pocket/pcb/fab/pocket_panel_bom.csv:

Comment,Designator,Footprint,LCSC Part #
"TYPE-C-31-M-12 USB-C 16P","J1","USB_C_Receptacle_HRO_TYPE-C-31-M-12","C165948"
"5.1k 1% 0402","R1,R2","R_0402_1005Metric","C25905"
"PRTR5V0U2X ESD (D+/D-/VBUS)","U1","SOT-143","C2827688"

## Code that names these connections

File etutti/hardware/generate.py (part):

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# 7, 8, 18-21, 23, and of its SD card, 10-13):
SEL_PINS = ["0", "1", "2", "3"]        # multiplexer address S0..S3, shared by all three
COM_PINS = ["14", "15", "16"]          # multiplexer 1..3 output -> A0, A1, A2
LED_PINS = {"4": "LED_R_DRV", "5": "LED_G_DRV"}  # bicolour power LED, through 330 ohm
# The controls board (pot, encoder, LED) under the interface lid, through
# J3. The firmware doesn't read the pot or encoder yet; these are the free
# pins kept for them (22 = A8 for the pot; 6 is the Audio Board's optional
# memory chip select: leave that chip unfitted).
CONTROL_PINS = {"22": "POT", "17": "ENC_A", "9": "ENC_B", "6": "ENC_SW"}
AUDIO_PINS = {"7", "8", "18", "19", "20", "21", "23"}  # Audio Board Rev D
# J3, JST PH 2.0 mm 8-pin vertical: pin -> net
J3_PINS = {1: "VCC", 2: "GND", 3: "POT", 4: "ENC_A", 5: "ENC_B", 6: "ENC_SW", 7: "LED_R", 8: "LED_G"}

# CD74HC4067 pin functions (SOIC-24). Channel n is "I<n>".
MUX_PINS = {1: "COM", 2: "I7", 3: "I6", 4: "I5", 5: "I4", 6: "I3", 7: "I2", 8: "I1", 9: "I0",
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        (f"{len(ks)} keys · C-griff G3–E6 · hex grid, pitch {U} mm, rows {ROW_PITCH:.2f} mm apart · board {PCB_THICKNESS} mm, shaped to the case", 13, "400"),
        (f"{len(ks)} × Gateron magnetic switch (no pins) · {len(ks)} × DRV5056A3 sensor on the BACK · 3 × CD74HC4067 + AMS1117-3.3 on the back (dashed)", 13, "400"),
        ("Key label: switch · MUX/channel · - - - plate edge · dashed blue: bottom-plate pillars (no parts on the back there)", 13, "400"),
        ("Mux address S0..S3 → pins " + ", ".join(SEL_PINS) + " · MUX1/2/3 output → pins " + ", ".join(COM_PINS) + " · J3: pot 22, encoder 17/9/6, LED 4/5", 13, "400"),
    ]
    y = h + 40
    for text, size, weight in lines:
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
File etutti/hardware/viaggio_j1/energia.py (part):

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    "L201": (73.75, 9.0, 90),
    # output cap of U204: VOUT pad right above pin 1, GND pad towards the PowerPAD
    "C208": (69.70, 6.0, 180),
    # input cap of U204 (VSYS, 10 uF, same part as C206): VIN pad right under pin 5
    "C202": (69.60, 12.25, 180),
    # battery cap of U202: VBAT pad facing pins 2/3, GND pad facing pin 4
    "C203": (65.45, 9.30, 270),
    # VINA filter of U204 next to pins 8 (VINA) / 7 (GND), R216 right above it
    "C209": (67.00, 8.75, 270),
    "R216": (67.00, 6.85, 270),
    # +3V3 bulk cap (was on the input side of U204)
    "C207": (65.40, 13.90, 0),
    # VSYS cap north of the block, its VSYS pad next to R216
    "C206": (64.67, 5.18, 180),
    # out of the corridor west of the charger's OUT pins (10/11), where the VSYS vias go
    "C213": (54.58, 7.17, 180),
    "C205": (58.58, 6.83, 180),
}
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    T("+3V3", BC, [(68.075, 8.0), (68.0, 7.25)], 0.2, "U204.10 FB -> via")
    Vv("+3V3", 68.0, 7.25, "U204.10 FB -> In2")
    # input: VIN (pin 5) straight down to C202.1; C202.2 to the PowerPAD's bottom finger
    T("VSYS", BC, [(70.875, 10.0), (70.875, 10.55)], 0.3, "U204.5 VIN -> C202.1 (saida do pino)")
    T("VSYS", BC, [(70.875, 10.55), (70.6, 11.75)], 0.8, "U204.5 VIN -> C202.1")
    T("GND", BC, [(68.75, 11.6), (69.225, 10.6)], 0.4, "C202.2 -> PowerPAD (dedo de baixo)")
    # VINA filter: pin 8 -> C209.1 <- R216.2; C209.2 -> pin 7
    T("BB_VINA", BC, [(68.075, 9.0), (67.85, 9.0), (67.2, 8.4)], 0.2, "U204.8 VINA -> C209.1")
    T("BB_VINA", BC, [(67.0, 7.36), (67.0, 8.27)], 0.2, "R216.2 -> C209.1")
    T("GND", BC, [(67.0, 9.3), (67.5, 9.5), (68.075, 9.5)], 0.2, "C209.2 -> U204.7")
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    # IN (pin 13) -> C201.1
    T("VBUS", BC, [(61.25, 7.562), (61.1, 6.55)], 0.3, "U202.13 IN -> C201.1 (saida do pino)")
    T("VBUS", BC, [(61.1, 6.55), (60.4, 5.8)], 0.8, "U202.13 IN -> C201.1")
    # BAT (pins 2/3) -> C203.1; GND pin 4 -> C203.2
    T("VBAT", BC, [(63.438, 8.75), (63.438, 9.25)], 0.24, "U202.2-3 BAT")
    T("VBAT", BC, [(63.438, 9.0), (64.35, 8.85)], 0.3, "U202.2/3 BAT -> C203.1 (saida do pino)")
    T("VBAT", BC, [(64.35, 8.85), (65.3, 8.5)], 0.8, "U202.2/3 BAT -> C203.1")
    T("GND", BC, [(63.438, 9.75), (64.2, 10.15), (64.9, 10.25)], 0.3, "U202.4 -> C203.2")
    # ---- GND vias at every cap's GND pad, +3V3 vias at the +3V3 pads (In2 plane)
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    """U204.L1 -> L201.1 and U204.L2 -> L201.2 in B.Cu (the chip's layer), no vias. 0.24 only from the
    pin to the edge of U204's courtyard; 0.8 from there into the inductor pad."""
    T = g.track
    T("BB_L2", BC, [(70.875, 8.5), (71.75, 8.5)], 0.24, "U204.2 L2 (saida do pino)")
    T("BB_L2", BC, [(71.75, 8.4), (72.6, 8.4)], 0.8, "U204.2 L2 -> L201.2")
    T("BB_L1", BC, [(70.875, 9.5), (71.75, 9.5)], 0.24, "U204.4 L1 (saida do pino)")
    T("BB_L1", BC, [(71.75, 9.65), (72.6, 9.65)], 0.8, "U204.4 L1 -> L201.1")


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

def step_c(g, fails):
    """VBUS, VSYS, VBAT. VSYS leaves the charger's OUT pins (10/11, west side) by two vias in the
    corridor freed there; the rest is the grid router, Corrente at 0.8 outside the courtyards."""
    T, Vv = g.track, g.via
    T("VSYS", BC, [(60.562, 8.75), (60.562, 9.25)], 0.24, "U202.10-11 OUT")
    T("VSYS", BC, [(60.562, 9.0), (59.5, 9.0)], 0.3, "U202.10/11 OUT (saida do pino)")
    T("VSYS", BC, [(59.5, 9.0), (58.6, 9.0)], 0.8, "U202.10/11 OUT -> vias")
    Vv("VSYS", 59.3, 9.0, "U202 OUT -> F.Cu")
    Vv("VSYS", 58.6, 9.0, "U202 OUT -> F.Cu")
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        has_pad = any(p.GetNetname() == n and REG[0] <= TOMM(p.GetPosition().x) <= REG[2]
                      and REG[1] <= TOMM(p.GetPosition().y) <= REG[3] for p in g.b.GetPads())
        (local if has_pad else through).append(n)
    # nets whose pins face each other across a part (VOL_SW_N: R210.2 under D205 to D205.3) first
    local = [n for n in PRIORITY if n in local] + [n for n in local if n not in PRIORITY]
    route_nets(g, local + through, fails)
    g.stitch = joins_and_stitch(g, fails, None)
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
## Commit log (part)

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2026-06-17 Add comprehensive README documentation
2026-06-17 Add CNAME for beatconfused.com domain
